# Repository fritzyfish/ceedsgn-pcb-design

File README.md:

# Final Project PCB Design

- AGULTO, Juliana Marie
- AVELINO, Joris Gabriel
- DURIMAN, Fritz Edward
- GUTIERREZ, Gian Carlo

## Guide

1. Open "FinalProject.kicad_pro"
2. To view schematic implementation, choose "FinalProject.kicad_sch"
3. To view the PCB implementation, choose "FinalProject.kicad_pcb"

## Results

**Schematic Implementation**
<br/><br/>

**PCB Implementation**

<br/><br/>

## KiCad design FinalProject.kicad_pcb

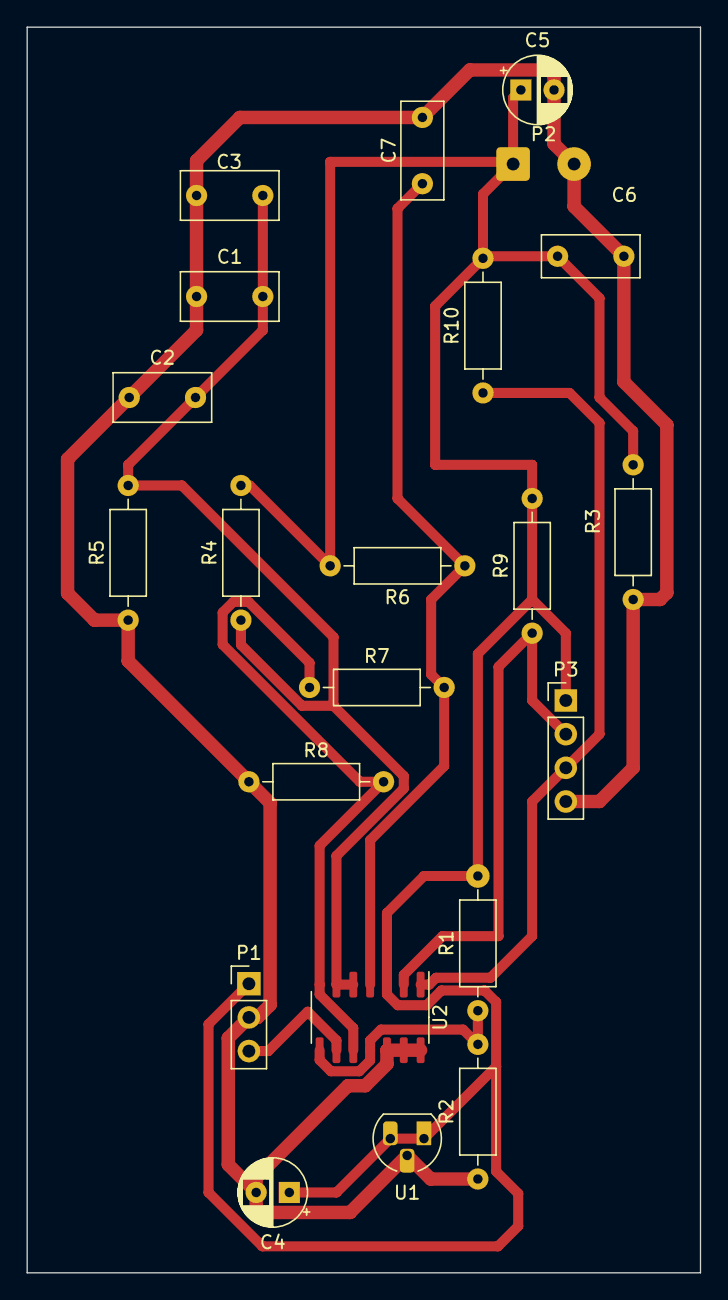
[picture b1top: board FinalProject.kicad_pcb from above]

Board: 2 copper layers, 50.8 x 94.0 mm, 22 parts (0 on the bottom side), 9 nets.

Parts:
C1, C2, C3: 1uF 25V; C_Rect_L7.2mm_W3.5mm_P5.00mm_FKS2_FKP2_MKS2_MKP2
C4: 10uF 16V; CP_Radial_D5.0mm_P2.50mm
C5: 47uF 16V; CP_Radial_D5.0mm_P2.50mm
C6, C7: 0.1uF 25V; C_Rect_L7.2mm_W3.0mm_P5.00mm_FKS2_FKP2_MKS2_MKP2
P1: Conn_01x03; PinHeader_1x03_P2.54mm_Vertical
P2: Conn_01x02; SolderWire-0.5sqmm_1x02_P4.6mm_D0.9mm_OD2.1mm
P3: Conn_01x04; PinHeader_1x04_P2.54mm_Vertical
R1: 9.1k 1/4W; R_Axial_DIN0207_L6.3mm_D2.5mm_P10.16mm_Horizontal
R2: 10k 1/4W; R_Axial_DIN0207_L6.3mm_D2.5mm_P10.16mm_Horizontal
R3, R7: 4.7k 1/4W; R_Axial_DIN0207_L6.3mm_D2.5mm_P10.16mm_Horizontal
R4, R5: 82k 1/4W; R_Axial_DIN0207_L6.3mm_D2.5mm_P10.16mm_Horizontal
R6, R8: 47k 1/4W; R_Axial_DIN0207_L6.3mm_D2.5mm_P10.16mm_Horizontal
R9, R10: 2.4k 1/4W; R_Axial_DIN0207_L6.3mm_D2.5mm_P10.16mm_Horizontal
U1: L78L05_TO92; TO-92L_HandSolder
U2: LM339; SOIC-14_3.9x8.7mm_P1.27mm

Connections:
GND: C1.1, C2.1, C3.1, C4.2, C5.2, C6.2, C7.2, P1.2, P2.2, P3.4, R2.1, R3.1, R5.1, R8.1, U1.2 (GND), U2.12 (V-), U2.13, U2.14
unnamed: C4.1, C5.1, C6.1, P1.1, P2.1, P3.1, R1.2, R3.2, R4.2, R6.2, R9.2, R10.2, U1.1 (VO), U1.3 (VI), U2.3 (V+)
unnamed: P1.3, U2.9 (+)
unnamed: P3.2, R9.1, U2.2
unnamed: P3.3, R10.1, U2.1
unnamed: C1.2, C2.2, C3.2, R4.1, R5.2, U2.5 (+), U2.6 (-)
unnamed: C7.1, R6.1, R7.2, U2.4 (-)
unnamed: R7.1, R8.2, U2.7 (+), U2.10 (-)
unnamed: R1.1, R2.2, U2.8 (-), U2.11 (+)

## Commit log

2023-08-09 Update Joris Avelino
2023-08-10 update ulet
2023-08-10 dalawa nalang
2023-08-10 may dalawang jumper ;-;
2023-08-10 edit
2023-08-10 updated wire sizes
2023-08-11 delete
2023-08-11 changed files names and deleted extra files
2023-08-11 deleted extra files
2023-08-11 added result images
2023-08-11 added jumpers to pcb
2023-08-11 replaced pcb image
2023-08-11 Fix: image
2023-08-14 FinalProject2
    need nalang ayusin yung pagka-arrange
2023-08-14 GRN thickness changed to 40mils
2023-08-14 may nakaligtaan akong 1 wire asdasdadsf
2023-08-14 40 na yung GRD(2)
2023-08-14 updated PCB tracks
2023-08-14 changed file names and deleted previous version
2023-08-14 new PCB image
